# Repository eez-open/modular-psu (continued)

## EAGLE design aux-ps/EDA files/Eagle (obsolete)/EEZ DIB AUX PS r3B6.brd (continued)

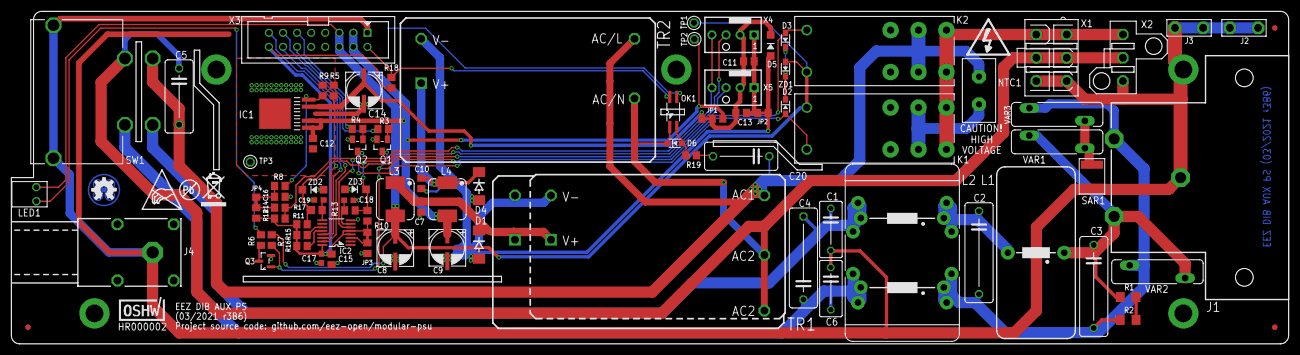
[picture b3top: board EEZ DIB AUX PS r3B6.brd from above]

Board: 2 copper layers, 230.5 x 60.0 mm, 93 parts (0 on the bottom side), 47 nets.

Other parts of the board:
EEZ_SIGNATURE: SIGNATURESMALL; SIGNATURE_5MM
U$2: PB_SMALL
U$3: RECYCLE_BIN1/8
U$4: ESD_SYMBOL

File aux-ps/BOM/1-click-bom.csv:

References,Qty,Description,Manufacturer,MPN,Manufacturer,MPN,Manufacturer,MPN,Manufacturer,MPN,Digikey,Mouser,RS,Newark,Farnell
"C1, C6",2,2n2 (Y2),,VY2222M31Y5VS63V7,,CY2Y-2N2,,,,,,,,,
"C17, C18",2,100n,,C0603C104K4RAC7081,,490-4774-1-ND,,VJ0603Y104KXJAT,,CL10B104KA8NNNC,,,,,
"C2, C3, C4",3,100n (X2),,R46KI310000M1M,,399-6806-ND,,F863BC104K310Z,,R46KI310000M1M,,,,,
C5,1,47n/400V (X2),,B32921C3473K000,,399-11478-ND,,B32921C3473M000,,MKP-X2-47NR10/310,,,,,
"C7, C10, C11, C15, C16",5,1u,,VJ0805Y105KXXTW1BC,,587-1283-1-ND,,C0805C105K4RACTU,,CL21B105KOFNNNE,,,,,
"C8, C9, C14",3,EEEFK1V470P,,EEEFK1V470P,,PCE3842CT-ND,,EEEFK1V470P,,EEEFK1V470P,,,,,
"D2, D3",2,BAS316,,"BAS316,115",,1727-7370-1-ND,,"BAS316,115",,"BAS316,115",,,,,
D5,1,SKL14,,PMEG4010EGWX,,1727-7335-1-ND,,PMEG4010EGWX,,SKL14-DIO,,,,,
IC1,1,BD00FC0WFP-E2,,BD00FC0WFP-E2,,BD00FC0WFP-E2CT-ND,,BD00FC0WFP-E2,,-,,,,,
IC2,1,MAX31760AEE+,,MAX31760AEE+,,MAX31760AEE+-ND,,-,,,,,,,
J1,1,PF0030/PC,,PF0030/PC,,708-1914-ND,,PF0030/PC,,PF0030/PC,,,,,
"J2, J3",2,1-726388-2,,1-726388-2,,A121493-ND,,1-726388-2,,61-3162-11/0030,,,,,
J4,1,SWEB 8094 AU/GN,,-,,SWEB 8094 AU/GN,,,,,,,,,
"K1, K2",2,RT424005,,RT424005,,PB1998-ND,,RT424005,,,,,,,
L1,1,2200HT-221-V-RC,,2200HT-221-V-RC,,2200HT-221-V-RC-ND,,-,,,,,,,
L2,1,RN222-4-02-3M3,,RN222-4-02-3M3,,817-2209-ND,,RN222-4-02-3M3,,-,,,,,
"L3, L4",2,VLS6045AF-3R3N,,IHLP2020CZER3R3M11,,445-180834-1-ND,,HPI0630-3R3,,,,,,,
LED1,1,WP934CB/YD,,754-1300-ND,,L-934CB/1YD,,,,,,,,,
NTC1,1,B57236S0200M,,B57236S0200M,,495-3047-ND,,B57236S0200,,,,,,,
"Q1, Q2",2,MMBT5551,,MMBT5551LT1G,,MMBT5551LT1GOSCT-ND,,MMBT5551LT1G,,MMBT5551,,,,,
Q3,1,2N7002,,2N7002-7-F,,2N7002LT1GOSCT-ND,,2N7002LT1G,,2N7002LT1G,,,,,
"R1, R2",2,470K,,MCWR12X4703FTL,,CRGCQ1206F470K,,CRG1206F470K,,1206S4J0474T5E,,,,,
"R12, R15",2,4K7,,CRGCQ0805F4K7,,311-4.70KCRCT-ND,,CRG0805F4K7,,0805S8F4701T5E,,,,,
R13,1,10R,,RC1206FR-0710RL,,311-10.0CRCT-ND,,CR1206-FX-10R0ELF,,CRCW120610R0FKTABC,,,,,
"R3, R4, R10, R11, R14",5,1K,,WCR0805-1K0FI,,RC0805FR-071KL,,CRG0805F1K0,,RC0805FR-071K,,,,,
"R5, R7",2,39K,,MCWR08X3902FTL,,RMCF0805FT39K0CT-ND,,CRCW080539K0FKEA,,0805S8J0393T5E,,,,,
R6,1,470R,,WCR0805-470RFI,,311-470CRCT-ND,,CRG0805F470R,,RC0805FR-07470R,,,,,
"R8, R9",2,3K3,,MCWR08X3301FTL,,A129755CT-ND,,CRG0805F3K3,,805S8F3301T5E,,,,,
SAR1,1,2051-47-SM-RPLF,,2051-47-SM-RPLFCT-ND,,-,,,,,,,,,
SW1,1,DF62J12S2AHQA,,DF62J12S2AHQA,,CKN2062-ND,,DF62J12S2AHQA,,DF62J12S2AHQA,,,,,
TR1,1,IRM-10-5,,IRM-10-5,,1866-3032-ND,,IRM-10-5,,IRM-10-5,,,,,
TR2,1,IRM-10-12,,IRM-10-12,,1866-3028-ND,,IRM-10-12,,IRM-10-12,,,,,
"VAR1, VAR2, VAR3",3,ERZE14A431 or V275LA20AP,,ERZE11A431,,P16688-ND,,ERZE11A431,,V275LA20AP,,,,,
X1,1,39-28-1063,,39-28-1063,,WM3802-ND,,39-28-1063,,MX-5566-06A,,,,,
X2,1,39-30-1039,,39-30-1039,,WM18442-ND,,39-30-1039,,MX-5566-03A3,,,,,
X3,1,DS1013-16SSIB1,,MC-254-16-00-ST-DIP,,ED10523-ND,,61201621621,,DS1013-16SSIB,,,,,
X4; fan connector,1,22-27-2031,,22-27-2031,,WM4112-ND,,22-27-2031,,MX-6410-03A,,,,,
ZD1,1,MM3Z18VT1G,,MM3Z18VT1G,,MM3Z18VT1GOSCT-ND,,MM3Z18VT1G,,MM3Z18VT1G,,,,,

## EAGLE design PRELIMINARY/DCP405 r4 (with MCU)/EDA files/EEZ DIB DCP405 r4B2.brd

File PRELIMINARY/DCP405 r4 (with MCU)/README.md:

### Preliminary design

A new version of the [EEZ DIB DCP405](https://www.envox.eu/dc-power-modules/dcp405-power-module/) power module that has its own MCU and improved external/remote programming (now for both CV and CC modes). This is a preliminary design that has been tested, but for which firmware needs to be developed. Once the design is complete, it will be moved to the [main](https://github.com/eez-open/modular-psu/tree/master/dcp405) folder of this module.

### TODO

* BOM list
* Firmware for on-board STM32F373
* Add support into the main (MCU module) firmware
* Front panel layout update (if necessary)

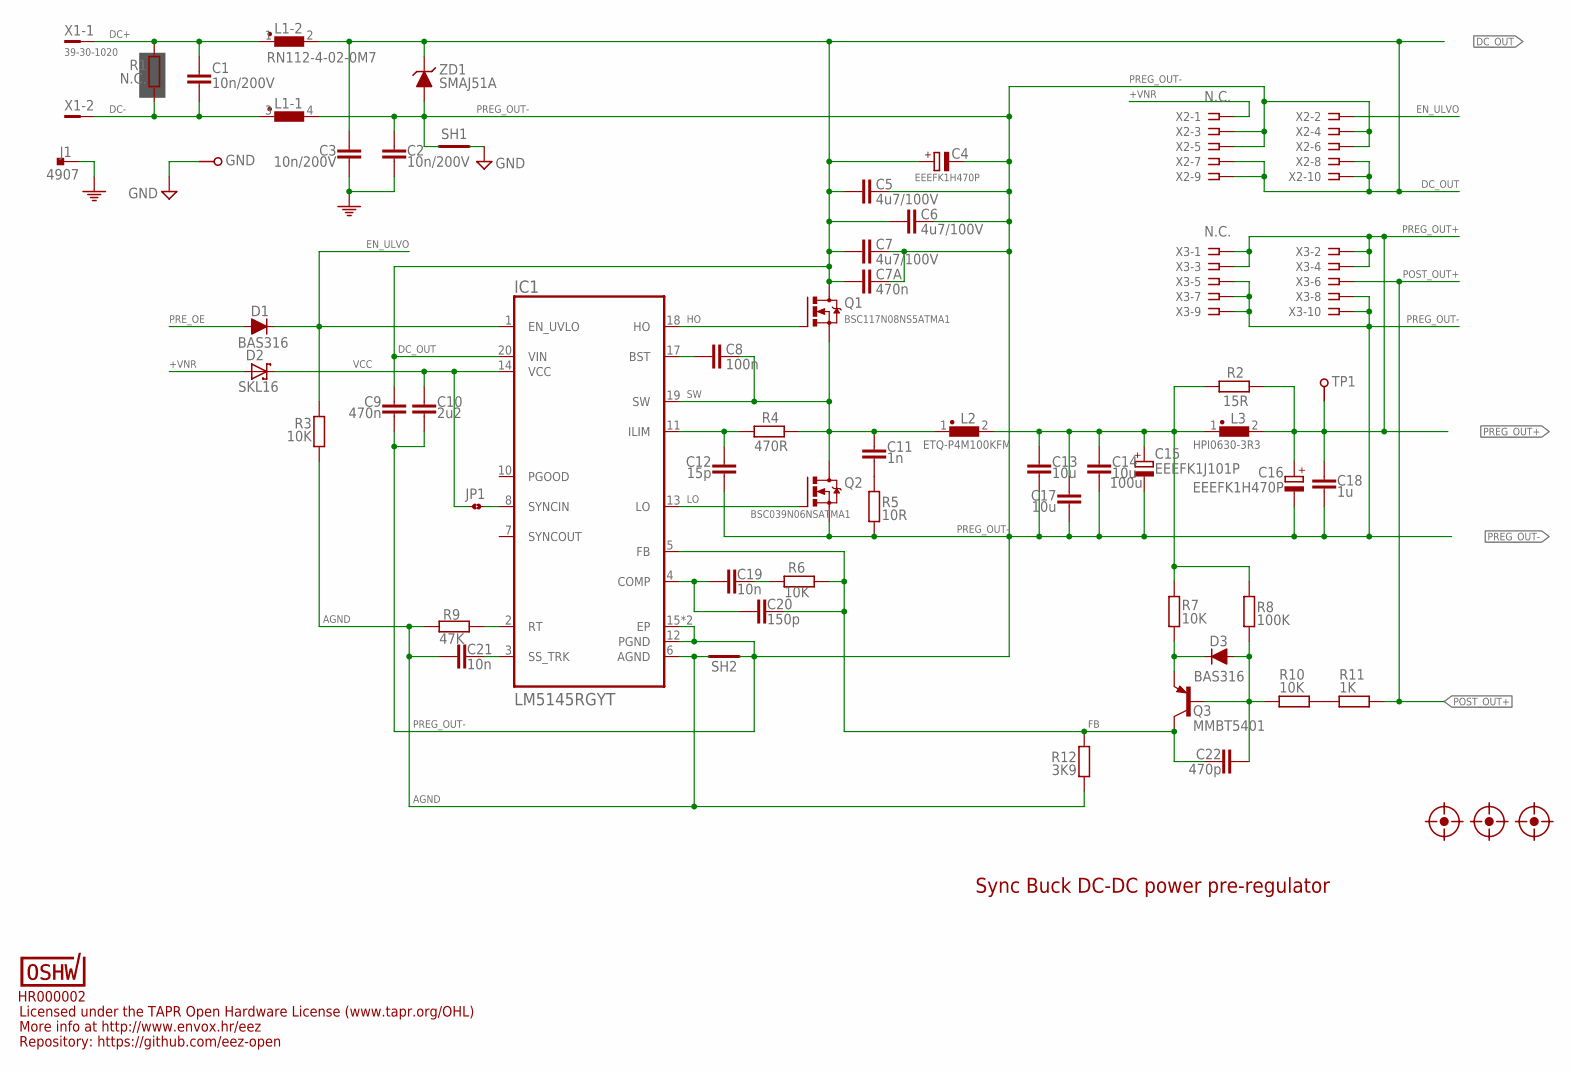
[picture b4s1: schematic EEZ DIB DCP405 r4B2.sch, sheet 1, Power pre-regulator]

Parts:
C1, C2, C3: 10n/200V; C1206
C4, C16: EEEFK1H470P; CAPAE830X1050N
C5, C6, C7: 4u7/100V; C1210
C7A, C9: 470n; C0805
C8: 100n; C0603
C10: 2u2; C1206
C11: 1n; C0805
C12: 15p; C0805
C13, C14, C17: 10u; C1210
C15: EEEFK1J101P; CAPAE1030X1050N
C18: 1u; C0805
C19, C21: 10n; C0805
C20: 150p; C0805
C22: 470p; C0805
D1, D3: BAS316; SOD323-R
D2: SKL16; SOD123
FM1, FM2, FM3: FIDUCIAL_2; FIDUCIAL_DUAL
GND: PCB_TEST_TABSHIELD; PCB_SHIELD_TAB
IC1: LM5145RGYT; RGY0020B
J1: 4907; PCB_TAB-4907
JP1: JP2-CUT-0805; R_0805
L1: RN112-4-02-0M7; RN112
L2: ETQ-P4M100KFM; PANASONIC_ETQ-P4_KFM
L3: HPI0630-3R3; COILCRAFT_HPI0630
OSHWA: HR000002; CERT-SMALL-SILK
Q1: BSC117N08NS5ATMA1; TDSON-8
Q2: BSC039N06NSATMA1; TDSON-8
Q3: MMBT5401; SOT23-BEC
R1: N.C.; R2512
R2: 15R; R2010
R3, R6, R7, R10: 10K; R0805
R4: 470R; R0805
R5: 10R; R1206
R8: 100K; R0805
R9: 47K; R0805
R11: 1K; R0805
R12: 3K9; R0805
SH1, SH2: SHORTNOHOLE; SHORT_NOHOLE
TP1: TEST-PIN_0.9MM
X1: 39-30-1020; MINIFIT_39301020
X2, X3: N.C.; SSW-105-02-S-D
ZD1: SMAJ51A; DO214AA

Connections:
+VNR: D2.A, X2.1; also elsewhere on the board
AGND: C21.2, IC1.6 (AGND), R3.1, R9.1, R12.2, SH2.1 (GND_A)
DC+: C1.2, L1.1, R1.2, X1.1
DC-: C1.1, L1.3 (1), R1.1, X1.2
DC_OUT: C3.2, C4.+, C5.1, C6.1, C7.1, C7A.2, C9.2, IC1.20 (VIN), L1.2, Q1.5 (D), Q1.6 (D), Q1.7 (D), Q1.8 (D), X2.7, X2.8, X2.9, X2.10, ZD1.C; also elsewhere on the board
EN_ULVO: D1.C, IC1.1 (EN_UVLO), R3.2, X2.2
FB: C20.1, C22.1, IC1.5 (FB), Q3.C, R6.2, R12.1
GND: GND.1, SH1.2 (GND_B); also elsewhere on the board
HO: IC1.18 (HO), Q1.4 (G)
LO: IC1.13 (LO), Q2.4 (G)
L_OUT: C13.1, C14.1, C15.+, C17.1, L2.2, L3.1, R2.2, R7.1, R8.1
unnamed: IC1.8 (SYNCIN), JP1.2
unnamed: R10.2, R11.1
unnamed: D3.C, Q3.E, R7.2
unnamed: C19.1, R6.1
unnamed: C8.1, IC1.17 (BST)
unnamed: IC1.2 (RT), R9.2
unnamed: C19.2, C20.2, IC1.4 (COMP)
unnamed: C12.1, IC1.11 (ILIM), R4.1
unnamed: C21.1, IC1.3 (SS_TRK)
unnamed: C11.2, R5.2
unnamed: C22.2, D3.A, Q3.B, R8.2, R10.1
PE: C2.2, C3.1, J1.1, J1.2; also elsewhere on the board
POST_OUT+: R11.2, X3.6; also elsewhere on the board
PREG_OUT+: C16.+, C18.2, L3.2, R2.1, TP1.1, X3.1, X3.2, X3.3, X3.4; also elsewhere on the board
PREG_OUT-: C2.1, C4.-, C5.2, C6.2, C7.2, C7A.1, C9.1, C10.1, C12.2, C13.2, C14.2, C15.-, C16.-, C17.2, C18.1, IC1.12 (PGND), IC1.15 (EP), IC1.21 (EP), L1.4 (2), Q2.1 (S), Q2.2 (S), Q2.3 (S), R5.1, SH1.1 (GND_A), SH2.2 (GND_B), X2.3, X2.4, X2.5, X2.6, X3.5, X3.7, X3.8, X3.9, X3.10, ZD1.A; also elsewhere on the board
PRE_OE: D1.A; also elsewhere on the board
SW: C8.2, C11.1, IC1.19 (SW), L2.1, Q1.1 (S), Q1.2 (S), Q1.3 (S), Q2.5 (D), Q2.6 (D), Q2.7 (D), Q2.8 (D), R4.2
VCC: C10.2, D2.C, IC1.14 (VCC), JP1.1

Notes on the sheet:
Licensed under the TAPR Open Hardware License (www.tapr.org/OHL)
Repository: https://github.com/eez-open
More info at http://www.envox.hr/eez
Sync Buck DC-DC power pre-regulator
100u

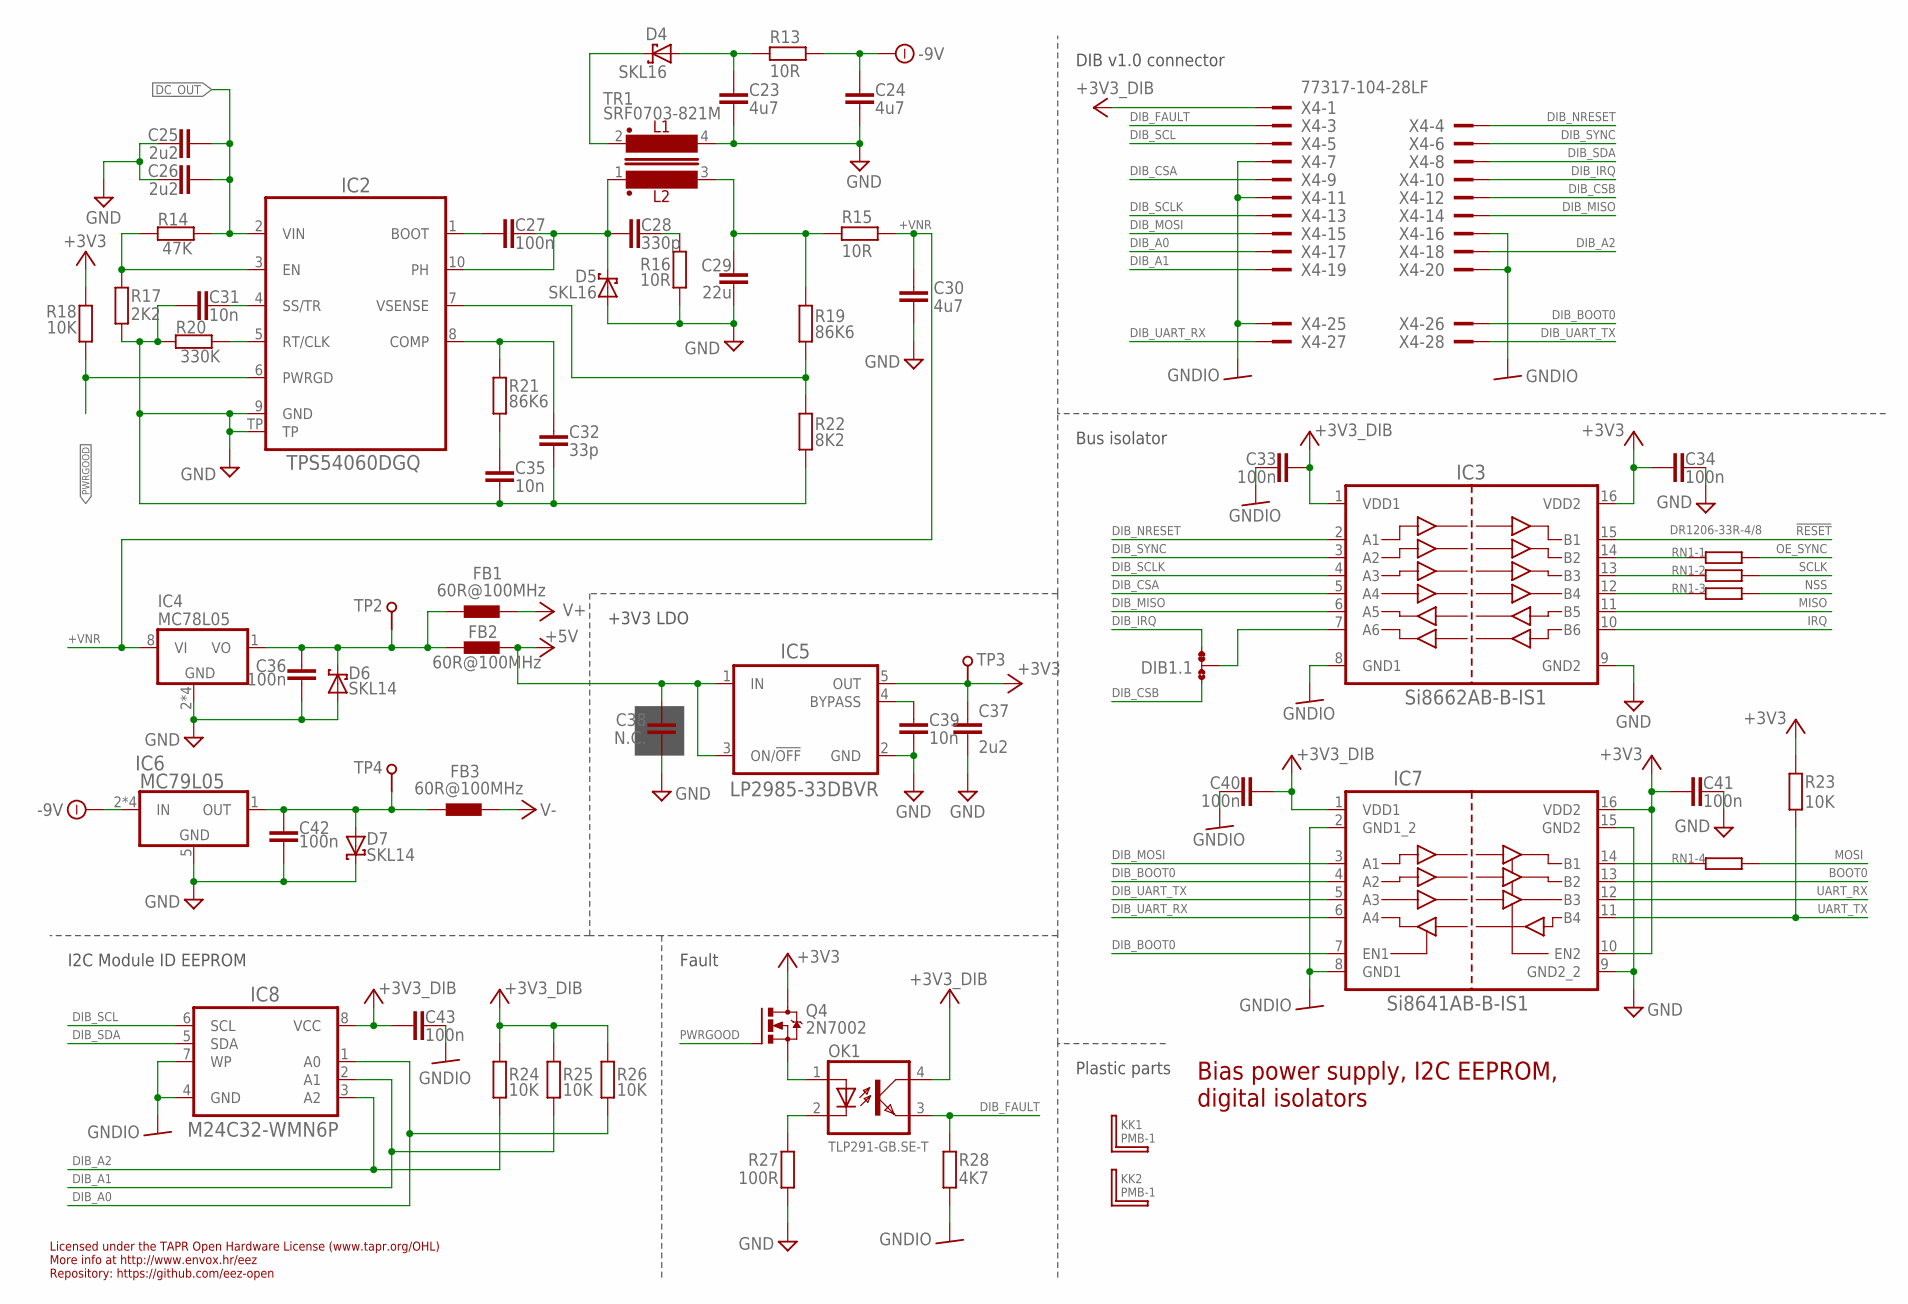
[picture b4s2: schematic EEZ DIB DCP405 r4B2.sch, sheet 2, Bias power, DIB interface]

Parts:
C23, C24, C30: 4u7; C1206
C25, C26, C37: 2u2; C1206
C27, C33, C34, C36, C40, C41, C42, C43: 100n; C0603
C28: 330p; C0805
C29: 22u; C1210
C31, C35, C39: 10n; C0805
C32: 33p; C0805
C38: N.C.; C0805
D4, D5: SKL16; SOD123
D6, D7: SKL14; SOD123
DIB1.1: JP3-CUT-0805-ROTATED; JP3-0805-CUT2
FB1, FB2, FB3: 60R@100MHz; BEAD0603
IC2: TPS54060DGQ; SOP50P490X110-11N
IC3: Si8662AB-B-IS1; SOIC-16
IC4: MC78L05; SOIC127P600X173-8N
IC5: LP2985-33DBVR; SOT95P270X145-5N
IC6: MC79L05; SOIC127P600X173-8N
IC7: Si8641AB-B-IS1; SOIC-16
IC8: M24C32-WMN6P; SOIC127P600X173-8N
KK1, KK2: PMB-1; PCB-MB
OK1: TLP291-GB.SE-T; SO4
Q4: 2N7002; SOT103P240X110-3N
R13, R15, R16: 10R; R1206
R14: 47K; R0805
R17: 2K2; R0805
R18, R23, R24, R25, R26: 10K; R0805
R19, R21: 86K6; R0805
R20: 330K; R0805
R22: 8K2; R0805
R27: 100R; R0805
R28: 4K7; R0805
RN1: DR1206-33R-4/8; CAY16
TP2, TP3, TP4: TEST-PIN_0.9MM
TR1: SRF0703-821M; SRF0703
X4: 77317-104-28LF

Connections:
!RESET: IC3.15 (B1); also elsewhere on the board
+3V3: C34.2, C37.1, C41.2, IC3.16 (VDD2), IC5.5 (OUT), IC7.10 (EN2), IC7.16 (VDD2), Q4.3 (D), R18.1, R23.2, TP3.1; also elsewhere on the board
+3V3_DIB: C33.1, C40.1, C43.2, IC3.1 (VDD1), IC7.1 (VDD1), IC8.8 (VCC), OK1.4 (COL), R24.1, R25.1, R26.1, X4.1
+5V: C38.2, FB2.P$2 (2), IC5.1 (IN), IC5.3 (ON/!OFF); also elsewhere on the board
+5VOUT: C36.1, D6.C, FB1.P$1 (1), FB2.P$1 (1), IC4.1 (VO), TP2.1
+VNR: C30.1, IC4.8 (VI), R15.1; also elsewhere on the board
-9V: C24.1, IC6.2 (IN), IC6.3 (IN), IC6.6 (IN), IC6.7 (IN), R13.1; also elsewhere on the board
BOOT0: IC7.13 (B2); also elsewhere on the board
DC_OUT: C25.1, C26.1, IC2.2 (VIN), R14.2; also elsewhere on the board
DIB_A0: IC8.1 (A0), R26.2, X4.17
DIB_A1: IC8.2 (A1), R25.2, X4.19
DIB_A2: IC8.3 (A2), R24.2, X4.18
DIB_BOOT0: IC7.4 (A2), IC7.7 (EN1), X4.26
DIB_CSA: IC3.5 (A4), X4.9
DIB_CSB: DIB1.1.NO, X4.12
DIB_FAULT: OK1.3 (EMIT), R28.2, X4.3
DIB_IRQ: DIB1.1.NC, X4.10
DIB_MISO: IC3.6 (A5), X4.14
DIB_MOSI: IC7.3 (A1), X4.15
DIB_NRESET: IC3.2 (A1), X4.4
DIB_SCL: IC8.6 (SCL), X4.5
DIB_SCLK: IC3.4 (A3), X4.13
DIB_SDA: IC8.5 (SDA), X4.8
DIB_SYNC: IC3.3 (A2), X4.6
DIB_UART_RX: IC7.6 (A4), X4.27
DIB_UART_TX: IC7.5 (A3), X4.28
GND: C23.2, C24.2, C25.2, C26.2, C29.2, C30.2, C31.2, C32.1, C34.1, C35.1, C36.2, C37.2, C38.1, C39.1, C41.1, C42.1, D5.A, D6.A, D7.C, IC2.9 (GND), IC2.TP, IC3.9 (GND2), IC4.2 (GND), IC4.3 (GND), IC4.6 (GND), IC4.7 (GND), IC5.2 (GND), IC6.5 (GND), IC7.9 (GND2_2), IC7.15 (GND2), R16.1, R17.1, R20.1, R22.1, R27.1, TR1.4; also elsewhere on the board
GNDIO: C33.2, C40.2, C43.1, IC3.8 (GND1), IC7.2 (GND1_2), IC7.8 (GND1), IC8.4 (GND), IC8.7 (WP), R28.1, X4.7, X4.11, X4.16, X4.20, X4.25
IRQ: IC3.10 (B6); also elsewhere on the board
MISO: IC3.11 (B5); also elsewhere on the board
MOSI: RN1.5 (2); also elsewhere on the board
unnamed: C39.2, IC5.4 (BYPASS)
unnamed: C28.2, R16.2
unnamed: C42.2, D7.A, FB3.P$1 (1), IC6.1 (OUT), TP4.1
unnamed: IC2.3 (EN), R14.1, R17.2
unnamed: C31.1, IC2.4 (SS/TR)
unnamed: IC2.5 (RT/CLK), R20.2
unnamed: C32.2, IC2.8 (COMP), R21.2
unnamed: C35.2, R21.1
unnamed: C27.2, IC2.1 (BOOT)
unnamed: IC2.7 (VSENSE), R19.1, R22.2
unnamed: OK1.2 (C), R27.2
unnamed: OK1.1 (A), Q4.2 (S)
unnamed: IC3.14 (B2), RN1.1
unnamed: IC3.13 (B3), RN1.2 (1)
unnamed: IC3.12 (B4), RN1.3 (1)
unnamed: IC7.14 (B1), RN1.4 (1)
unnamed: C23.1, D4.A, R13.2
unnamed: DIB1.1.COM, IC3.7 (A6)
NSS: RN1.6 (2); also elsewhere on the board
OE_SYNC: RN1.8 (2); also elsewhere on the board
PH: C27.1, C28.1, D5.C, IC2.10 (PH), TR1.1
PWRGOOD: IC2.6 (PWRGD), Q4.1 (G), R18.2; also elsewhere on the board
SCLK: RN1.7 (2); also elsewhere on the board
UART_RX: IC7.12 (B3); also elsewhere on the board
UART_TX: IC7.11 (B4), R23.1; also elsewhere on the board
V+: FB1.P$2 (2); also elsewhere on the board
V-: FB3.P$2 (2); also elsewhere on the board
VOUT+: C29.1, R15.2, R19.2, TR1.3
VOUT-: D4.C, TR1.2

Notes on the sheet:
Licensed under the TAPR Open Hardware License (www.tapr.org/OHL)
Repository: https://github.com/eez-open
More info at http://www.envox.hr/eez
I2C Module ID EEPROM
Bias power supply, I2C EEPROM, digital isolators
Plastic parts
Bus isolator
DIB v1.0 connector
+3V3 LDO
Fault

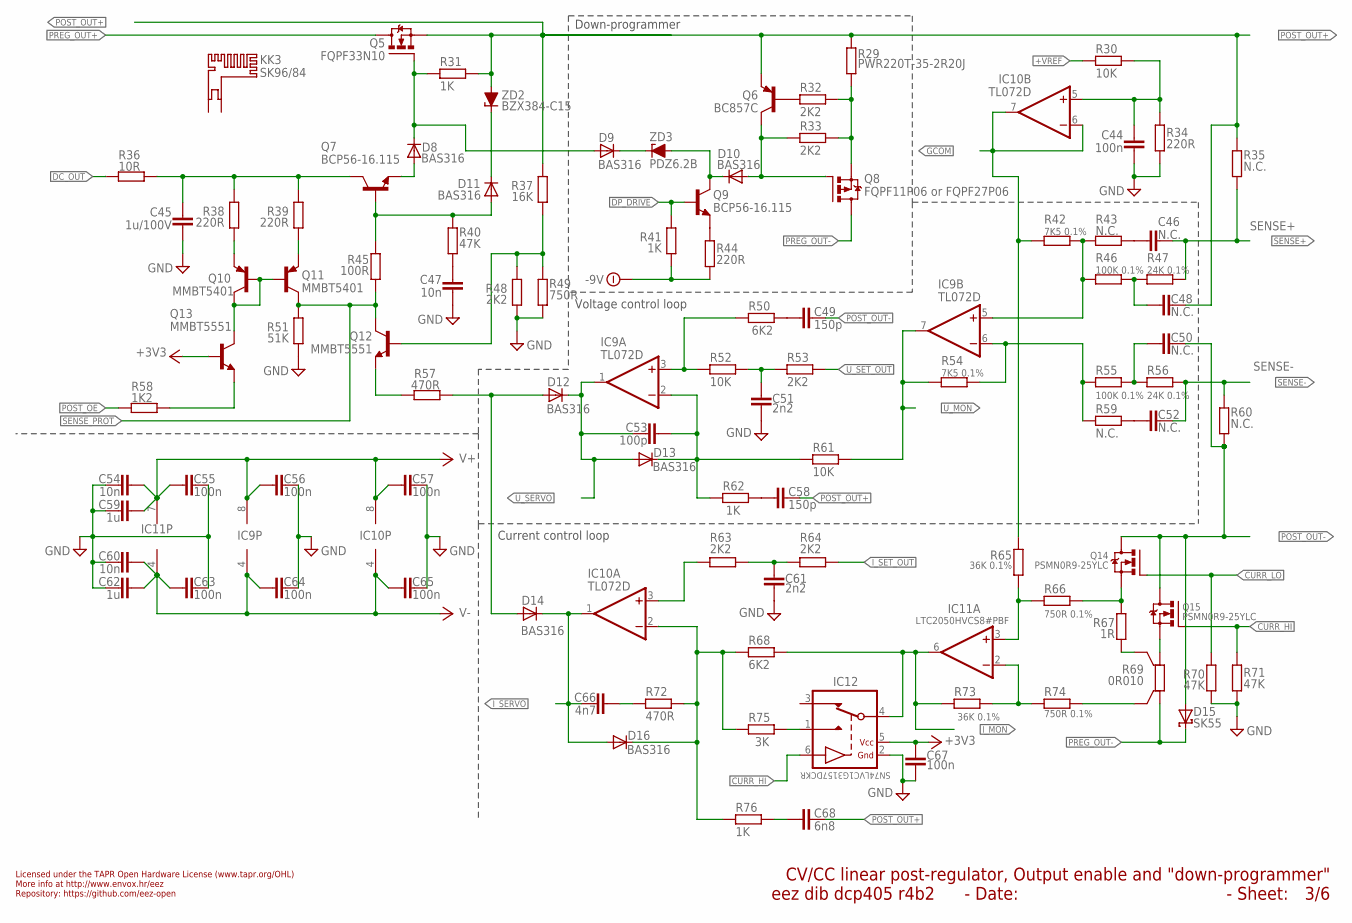
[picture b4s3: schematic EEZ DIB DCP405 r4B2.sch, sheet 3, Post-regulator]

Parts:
C44, C55, C56, C57, C63, C64, C65, C67: 100n; C0603
C45: 1u/100V; C1206
C46, C48, C50, C52: N.C.; C0805
C47, C54, C60: 10n; C0805
C49, C58: 150p; C0805
C51, C61: 2n2; C0805
C53: 100p; C0805
C59, C62: 1u; C0805
C66: 4n7; C0805
C68: 6n8; C0805
D8, D9, D10, D11, D12, D13, D14, D16: BAS316; SOD323-W
D15: SK55; SMB
IC9, IC10: TL072D; SOIC127P600X173-8N
IC11: LTC2050HVCS8#PBF; SOIC127P600X173-8N
IC12: SN74LVC1G3157DCKR; SOT65P210X110-6N
KK3: SK96/84
Q5: FQPF33N10; TO220FP-V
Q6: BC857C; SOT23-BEC
Q7, Q9: BCP56-16.115; SOT230P700X180-4N
Q8: FQPF11P06 or FQPF27P06; TO220FP-V
Q10, Q11: MMBT5401; SOT23-BEC
Q12, Q13: MMBT5551; SOT23-BEC
Q14, Q15: PSMN0R9-25YLC; SOT669
R29: PWR220T-35-2R20J; TO220-2R
R30, R52, R61: 10K; R0805
R31, R41, R62, R76: 1K; R0805
R32, R33, R48, R53, R63, R64: 2K2; R0805
R34, R38, R39, R44: 220R; R0805
R35, R43, R59, R60: N.C.; R0805
R36: 10R; R1206
R37: 16K; R0805
R40, R70, R71: 47K; R0805
R42, R54: 7K5 0.1%; R0805
R45: 100R; R0805
R46, R55: 100K 0.1%; R0805
R47, R56: 24K 0.1%; R0805
R49: 750R; R0805
R50, R68: 6K2; R0805
R51: 51K; R0805
R57, R72: 470R; R0805
R58: 1K2; R0805
R65, R73: 36K 0.1%; R0805
R66, R74: 750R 0.1%; R0805
R67: 1R; R1206
R69: 0R010; R_2512-4WIRE
R75: 3K; R0805
ZD2: BZX384-C15; SOD323-W
ZD3: PDZ6.2B; SOD323-W

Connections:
!DP_DRIVE: Q9.1 (B), R41.1; also elsewhere on the board
+3V3: C67.1, IC12.5 (VDD), Q13.B; also elsewhere on the board
+VREF: R30.1; also elsewhere on the board
-9V: R41.2, R44.2; also elsewhere on the board
CURR_HI: IC12.6 (CTRL), Q15.4 (G), R71.2; also elsewhere on the board
CURR_LO: Q14.4 (G), R70.2; also elsewhere on the board
DC_BIAS: C45.1, Q7.2 (C), Q7.4 (C), R36.2, R38.2, R39.2
DC_OUT: R36.1; also elsewhere on the board
GCOM: IC10.6 (-IN), IC10.7 (OUT), R42.1, R65.1; also elsewhere on the board
GND: C44.2, C45.2, C47.2, C51.2, C54.1, C55.2, C56.1, C57.1, C59.1, C60.1, C61.2, C62.1, C63.2, C64.1, C65.1, C67.2, IC12.2 (GND), R34.2, R48.1, R49.1, R51.1, R70.1, R71.1; also elsewhere on the board
ISENSE+: IC11.3 (+IN), R65.2, R66.2
ISENSE-: IC11.2 (-IN), R73.1, R74.2
I_MON: IC11.6 (OUT), IC12.4 (COM), R68.1, R73.2; also elsewhere on the board
I_SERVO: C66.2, D14.C, D16.A, IC10.1 (OUT); also elsewhere on the board
I_SET_OUT: R64.1; also elsewhere on the board
LOOP_CTRL: D12.A, D14.A, R57.1; also elsewhere on the board
unnamed: C61.1, R63.1, R64.2
unnamed: IC9.3 (+IN), R50.2, R52.2
unnamed: C53.1, D13.C, IC9.2 (-IN), R61.2, R62.2
unnamed: C50.1, R55.2, R56.1
unnamed: C48.1, R46.2, R47.1
unnamed: C46.2, R43.1
unnamed: IC12.1 (NO), R75.1
unnamed: IC10.3 (+IN), R63.2
unnamed: C52.2, R59.1
unnamed: C68.2, R76.1
unnamed: D16.C, IC10.2 (-IN), R68.2, R72.2, R75.2, R76.2
unnamed: C51.1, R52.1, R53.2
unnamed: C49.2, R50.1
unnamed: C58.2, R62.1
unnamed: D8.C, D9.A, Q5.1 (G), R31.1
unnamed: D8.A, Q7.3 (E)
unnamed: D11.A, Q7.1 (B), R40.2, R45.1
unnamed: D11.C, ZD2.C
unnamed: C47.1, R40.1
unnamed: D9.C, ZD3.C
unnamed: Q8.3 (S), R29.1, R32.1, R33.1
unnamed: D10.A, Q6.C, Q8.1 (G), R33.2
unnamed: Q12.E, R57.2
unnamed: Q11.E, R39.1
unnamed: Q10.E, R38.1
unnamed: Q13.E, R58.2
unnamed: Q12.B, R37.1, R48.2, R49.2
unnamed: Q9.3 (E), R44.1
unnamed: Q6.B, R32.2
unnamed: C66.1, R72.1
unnamed: C44.1, IC10.5 (+IN), R30.2, R34.1
unnamed: Q14.1 (S), Q14.2 (S), Q14.3 (S), R66.1, R67.2
unnamed: R67.1, R69.2S
unnamed: IC9.5 (+IN), R42.2, R43.2, R46.1
unnamed: IC9.6 (-IN), R54.2, R55.1, R59.2
unnamed: R69.1S, R74.1
POST_OE: R58.1; also elsewhere on the board
POST_OUT+: C48.2, C58.1, C68.1, Q5.3 (S), Q6.E, R29.2, R31.2, R35.1, R37.2, ZD2.A; also elsewhere on the board
POST_OUT-: C49.1, C50.2, D15.A, Q14.MB (D), Q15.MB (D), R60.2; also elsewhere on the board
PREG_OUT+: Q5.2 (D); also elsewhere on the board
PREG_OUT-: D15.C, Q8.2 (D), R69.1; also elsewhere on the board
Q7C1: Q10.B, Q10.C, Q11.B, Q13.C
Q8C: D10.C, Q9.2 (C), Q9.4 (C), ZD3.A
Q14S: Q15.1 (S), Q15.2 (S), Q15.3 (S), R69.2
SENSE+: C46.1, R35.2, R47.2; also elsewhere on the board
SENSE-: C52.1, R56.2, R60.1; also elsewhere on the board
SENSE_PROT: Q11.C, Q12.C, R45.2, R51.2; also elsewhere on the board
U_MON: IC9.7 (OUT), R54.1, R61.1; also elsewhere on the board
U_SERVO: C53.2, D12.C, D13.A, IC9.1 (OUT); also elsewhere on the board
U_SET_OUT: R53.1; also elsewhere on the board
V+: C54.2, C55.1, C56.2, C57.2, C59.2, IC9.8 (V+), IC10.8 (V+), IC11.7 (V+); also elsewhere on the board
V-: C60.2, C62.2, C63.1, C64.2, C65.2, IC9.4 (V-), IC10.4 (V-), IC11.4 (V-); also elsewhere on the board

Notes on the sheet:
Licensed under the TAPR Open Hardware License (www.tapr.org/OHL)
Repository: https://github.com/eez-open
More info at http://www.envox.hr/eez
CV/CC linear post-regulator, Output enable and "down-programmer"
- Sheet:
- Date:
Current control loop
Voltage control loop
Down-programmer

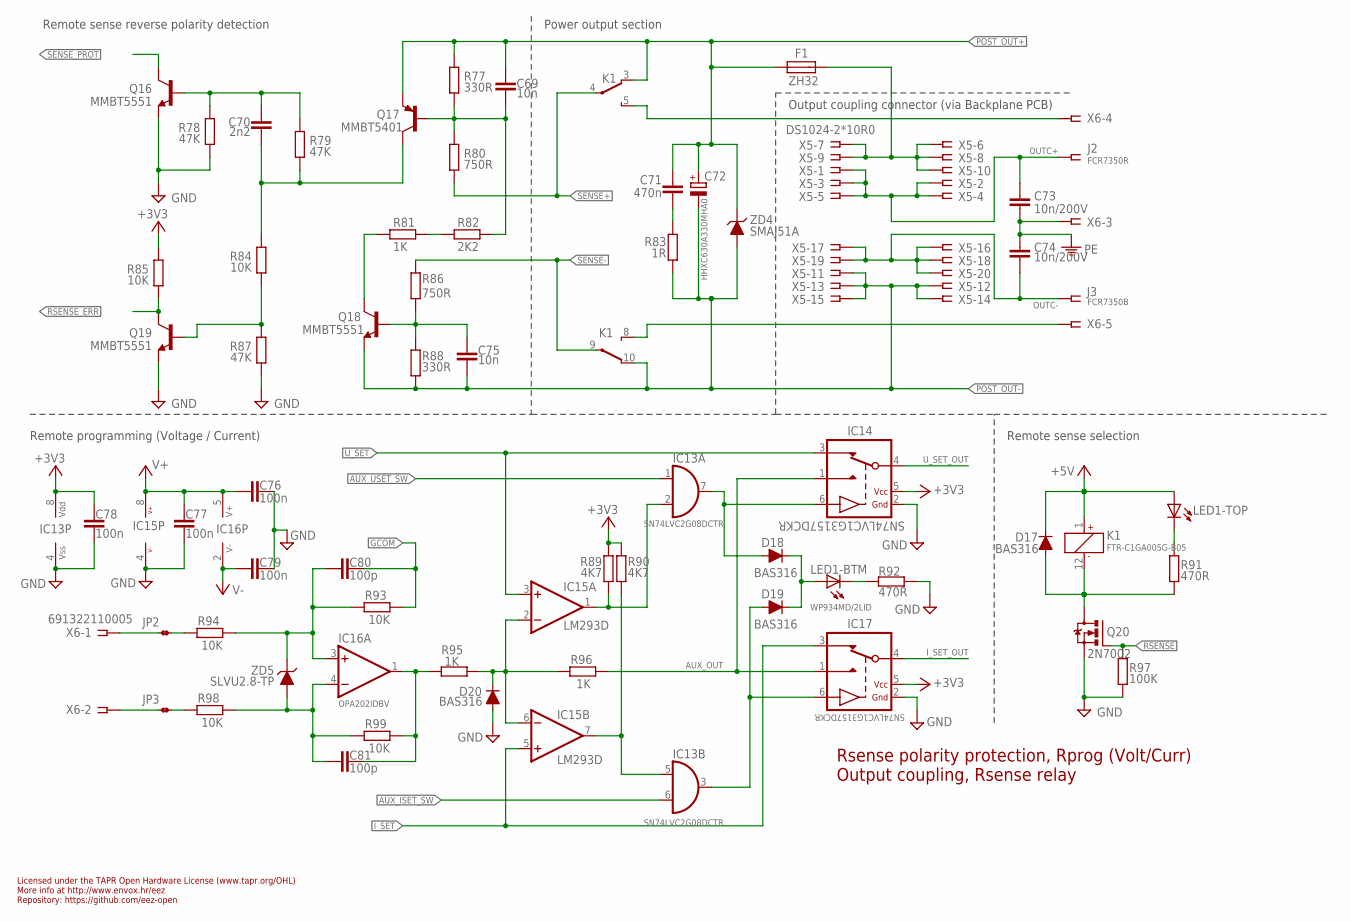
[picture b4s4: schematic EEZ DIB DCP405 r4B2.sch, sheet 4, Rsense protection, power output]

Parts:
C69, C75: 10n; C0805
C70: 2n2; C0805
C71: 470n; C0805
C72: HHXC630A330MHA0; CAPAE830X1050N
C73, C74: 10n/200V; C1206
C76, C77, C78, C79: 100n; C0603
C80, C81: 100p; C0805
D17, D18, D19, D20: BAS316; SOD323-R
F1: ZH32
IC13: SN74LVC2G08DCTR; DCT8
IC14, IC17: SN74LVC1G3157DCKR; SOT65P210X110-6N
IC15: LM293D; SOIC127P600X173-8N
IC16: OPA202IDBV; DBV5
J2: FCR7350R; S16N-PC
J3: FCR7350B; S16N-PC
JP2, JP3: JP2-NOCUT-0805; JP2-0805-NOCUT
K1: FTR-C1GA005G-B05; FTR-C1
LED1: WP934MD/2LID; WP934MD
Q16, Q18, Q19: MMBT5551; SOT23-BEC
Q17: MMBT5401; SOT23-BEC
Q20: 2N7002; SOT103P240X110-3N
R77, R88: 330R; R0805
R78, R79, R87: 47K; R0805
R80, R86: 750R; R0805
R81, R95, R96: 1K; R0805
R82: 2K2; R0805
R83: 1R; R1206
R84, R85, R93, R94, R98, R99: 10K; R0805
R89, R90: 4K7; R0805
R91, R92: 470R; R0805
R97: 100K; R0805
X5: DS1024-2*10R0; SSW-110-02-T-D-RA
X6: 691322110005; MC1,5/5-G-3,5
ZD4: SMAJ51A; DO214AA
ZD5: SLVU2.8-TP; SOT23

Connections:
+3V3: C78.2, IC13.8 (VDD), IC14.5 (VDD), IC17.5 (VDD), R85.2, R89.1, R90.1; also elsewhere on the board
+5V: D17.C, K1.1 (C1), LED1.TA (A); also elsewhere on the board
AUX_IN+: C80.2, IC16.3 (+IN), R93.2, R94.1, ZD5.3 (C)
AUX_IN-: C81.2, IC16.4 (-IN), R98.1, R99.2, ZD5.1 (A), ZD5.2 (A)
AUX_ISET_SW: IC13.6 (I1); also elsewhere on the board
AUX_OUT: IC14.1 (NO), IC17.1 (NO), R96.1
AUX_USET_SW: IC13.1 (I0); also elsewhere on the board
GCOM: C80.1, R93.1; also elsewhere on the board
GND: C76.2, C77.2, C78.1, C79.2, D20.A, IC13.4 (VSS), IC14.2 (GND), IC15.4 (V-), IC17.2 (GND), Q16.E, Q19.E, Q20.2 (S), R78.1, R87.1, R92.1, R97.1; also elsewhere on the board
I_SET: IC15.5 (+IN), IC17.3 (NC); also elsewhere on the board
I_SET_OUT: IC17.4 (COM); also elsewhere on the board
unnamed: JP3.1, X6.2
unnamed: D20.C, IC15.2 (-IN), IC15.6 (-IN), R95.1, R96.2
unnamed: C81.1, IC16.1 (OUT), R95.2, R99.1
unnamed: D18.C, D19.C, LED1.BA (A)
unnamed: JP2.2, R94.2
unnamed: JP2.1, X6.1
unnamed: JP3.2, R98.2
unnamed: IC13.2 (I1), IC15.1 (OUT), R89.2
unnamed: IC13.5 (I0), IC15.7 (OUT), R90.2
unnamed: D18.A, IC13.7 (O), IC14.6 (CTRL)
unnamed: D19.A, IC13.3 (O), IC17.6 (CTRL)
unnamed: C71.2, R83.2
unnamed: D17.A, K1.12 (C2), Q20.3 (D), R91.1
unnamed: K1.5 (NO), X6.4
unnamed: K1.8 (NO), X6.5
unnamed: LED1.TC (C), R91.2
unnamed: LED1.BC (C), R92.2
unnamed: C69.2, Q17.B, R77.1, R80.2, R82.2
unnamed: C70.2, Q17.C, R79.1, R84.2
unnamed: Q18.C, R81.1
unnamed: C75.1, Q18.B, R86.1, R88.2
unnamed: C70.1, Q16.B, R78.2, R79.2
unnamed: Q19.B, R84.1, R87.2
unnamed: R81.2, R82.1
OUTC+: C73.1, J2.1, X5.1, X5.2, X5.3, X5.4, X5.5
OUTC-: C74.2, J3.1, X5.16, X5.17, X5.18, X5.19, X5.20
OUTF+: F1.2, X5.6, X5.7, X5.8, X5.9, X5.10
PE: C73.2, C74.1, X6.3; also elsewhere on the board
POST_OUT+: C69.1, C71.1, C72.+, F1.1, K1.3 (NC), Q17.E, R77.2, ZD4.C; also elsewhere on the board
POST_OUT-: C72.-, C75.2, K1.10 (NC), Q18.E, R83.1, R88.1, X5.11, X5.12, X5.13, X5.14, X5.15, ZD4.A; also elsewhere on the board
RSENSE: Q20.1 (G), R97.2; also elsewhere on the board
RSENSE_ERR: Q19.C, R85.1; also elsewhere on the board
SENSE+: K1.4 (COM), R80.1; also elsewhere on the board
SENSE-: K1.9 (COM), R86.2; also elsewhere on the board
SENSE_PROT: Q16.C; also elsewhere on the board
U_SET: IC14.3 (NC), IC15.3 (+IN); also elsewhere on the board
U_SET_OUT: IC14.4 (COM); also elsewhere on the board
V+: C76.1, C77.1, IC15.8 (V+), IC16.5 (V+); also elsewhere on the board
V-: C79.1, IC16.2 (V-); also elsewhere on the board

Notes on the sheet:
Rsense polarity protection, Rprog (Volt/Curr) Output coupling, Rsense relay
Licensed under the TAPR Open Hardware License (www.tapr.org/OHL)
Repository: https://github.com/eez-open
More info at http://www.envox.hr/eez
Remote sense reverse polarity detection
Remote sense selection
Output coupling connector (via Backplane PCB)
Power output section
Remote programming (Voltage / Current)

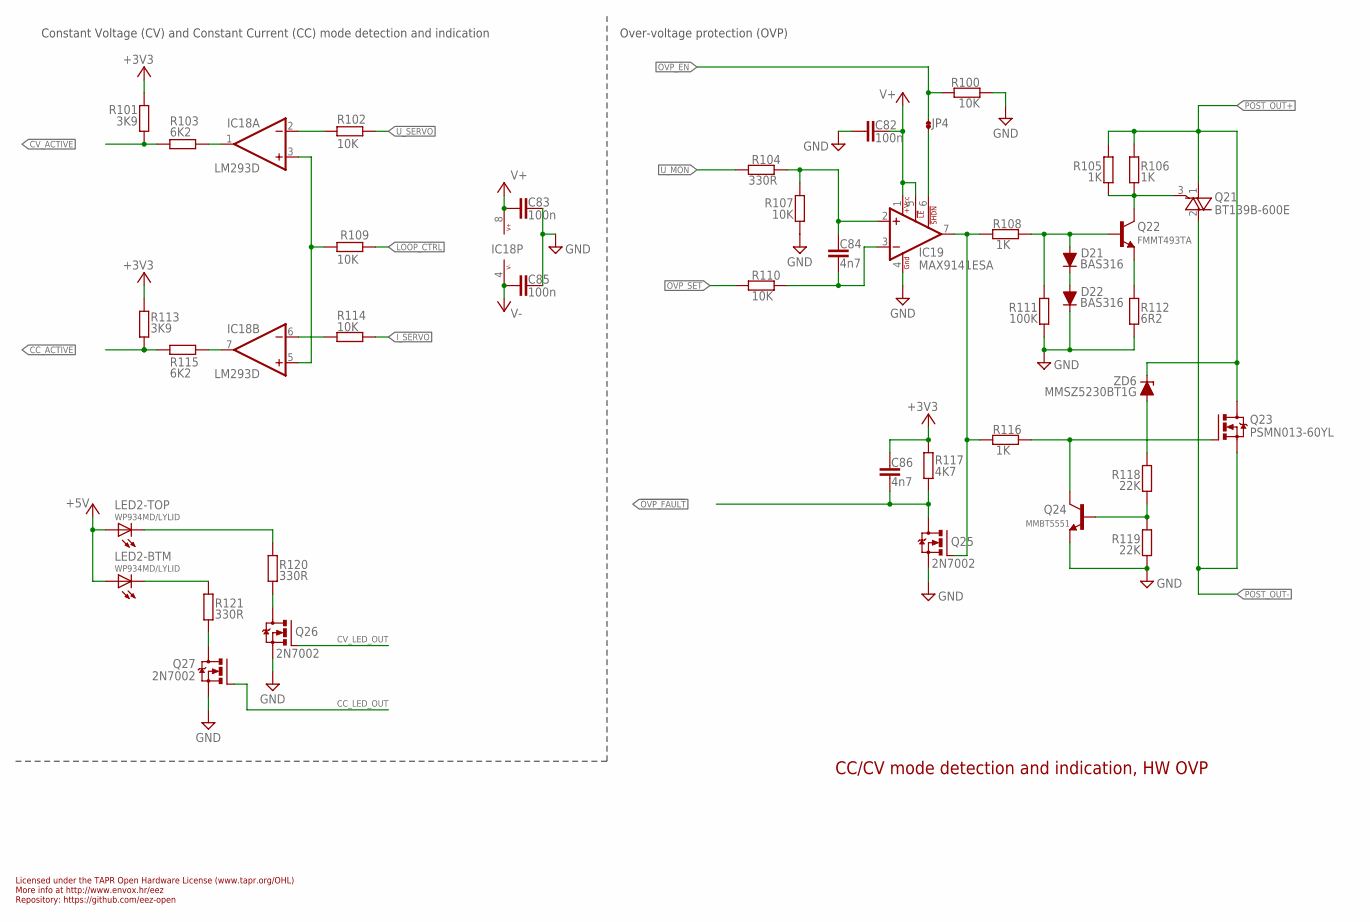
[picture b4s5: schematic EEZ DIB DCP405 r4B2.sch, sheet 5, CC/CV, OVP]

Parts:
C82, C83, C85: 100n; C0603
C84, C86: 4n7; C0805
D21, D22: BAS316; SOD323-R
IC18: LM293D; SOIC127P600X173-8N
IC19: MAX9141ESA; SOIC127P600X173-8N
JP4: JP2-NOCUT-0805; JP2-0805-NOCUT
LED2: WP934MD/LYLID; WP934MD
Q21: BT139B-600E; D2PAK
Q22: FMMT493TA; SOT23-BEC
Q23: PSMN013-60YL; SOT669
Q24: MMBT5551; SOT23-BEC
Q25, Q26, Q27: 2N7002; SOT103P240X110-3N
R100, R102, R107, R109, R110, R114: 10K; R0805
R101, R113: 3K9; R0805
R103, R115: 6K2; R0805
R104, R120, R121: 330R; R0805
R105, R106, R108, R116: 1K; R0805
R111: 100K; R0805
R112: 6R2; R0805
R117: 4K7; R0805
R118, R119: 22K; R0805
ZD6: MMSZ5230BT1G; SOD123

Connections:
!OVP_FAULT: C86.2, Q25.3 (D), R117.2; also elsewhere on the board
+3V3: C86.1, R101.2, R113.2, R117.1; also elsewhere on the board
+5V: LED2.BA (A), LED2.TA (A); also elsewhere on the board
CC_ACTIVE: R113.1, R115.2; also elsewhere on the board
CC_LED: LED2.BC (C), R121.2
CC_LED_OUT: Q27.1 (G); also elsewhere on the board
CV_ACTIVE: R101.1, R103.2; also elsewhere on the board
CV_LED_OUT: Q26.1 (G); also elsewhere on the board
D_CC: Q27.3 (D), R121.1
D_CV: Q26.3 (D), R120.2
GND: C82.1, C83.1, C85.1, D22.C, IC19.4 (GND), Q24.E, Q25.2 (S), Q26.2 (S), Q27.2 (S), R100.1, R107.2, R111.1, R112.1, R119.1; also elsewhere on the board
I_SERVO: R114.1; also elsewhere on the board
LOOP_CTRL: R109.2; also elsewhere on the board
unnamed: IC19.6 (!SHDN), JP4.2
unnamed: LED2.TC (C), R120.1
unnamed: IC19.7 (OUT), Q25.1 (G), R108.2, R116.2
unnamed: Q21.3 (G), Q22.C, R105.1, R106.1
unnamed: Q22.E, R112.2
unnamed: D21.C, D22.A
unnamed: D21.A, Q22.B, R108.1, R111.2
unnamed: R118.2, ZD6.A
unnamed: Q24.B, R118.1, R119.2
unnamed: IC18.1 (OUT), R103.1
unnamed: IC18.7 (OUT), R115.1
unnamed: Q23.4 (G), Q24.C, R116.1
unnamed: IC18.3 (+IN), IC18.5 (+IN), R109.1
unnamed: IC18.2 (-IN), R102.2
unnamed: IC18.6 (-IN), R114.2
OVP_EN: JP4.1, R100.2; also elsewhere on the board
OVP_IN+: C84.1, IC19.2 (+IN), R104.2, R107.1
OVP_IN-: C84.2, IC19.3 (-IN), R110.2
OVP_SET: R110.1; also elsewhere on the board
POST_OUT+: Q21.1 (A1), Q23.MB (D), R105.2, R106.2, ZD6.C; also elsewhere on the board
POST_OUT-: Q21.2 (A2), Q23.1 (S), Q23.2 (S), Q23.3 (S); also elsewhere on the board
U_MON: R104.1; also elsewhere on the board
U_SERVO: R102.1; also elsewhere on the board
V+: C82.2, C83.2, IC18.8 (V+), IC19.1 (+VCC), IC19.5 (!LE); also elsewhere on the board
V-: C85.2, IC18.4 (V-); also elsewhere on the board

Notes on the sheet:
Licensed under the TAPR Open Hardware License (www.tapr.org/OHL)
Repository: https://github.com/eez-open
More info at http://www.envox.hr/eez
CC/CV mode detection and indication, HW OVP
Constant Voltage (CV) and Constant Current (CC) mode detection and indication
Over-voltage protection (OVP)
